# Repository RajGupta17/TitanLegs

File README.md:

## Description

TitanLegs is a 4 legged Quadruped robot which requires BLDC motors to actuate. And this is a 4 layered BLDC Servo Controller PCB which can operate upto 60V; 100A. This board has in-built micro-controller (ESP32), Gate Driver (DRV8323RS) that drives the BLDC Motor, High Voltage MOSFETs, Encoders (AS5047P), CAN BUS IC, 60V to 3.3V (2.5A) Buck Converter (TPS54260), USB to UART (CP2102) communication for programming ESP32 with Type-C, and few internal circuitry.

## 3D Model:

## Schematic Design:

## PCB Layers:

### All Layers

## Mentor

* [Chinmay Lonkar](https://github.com/ChinmayLonkar)

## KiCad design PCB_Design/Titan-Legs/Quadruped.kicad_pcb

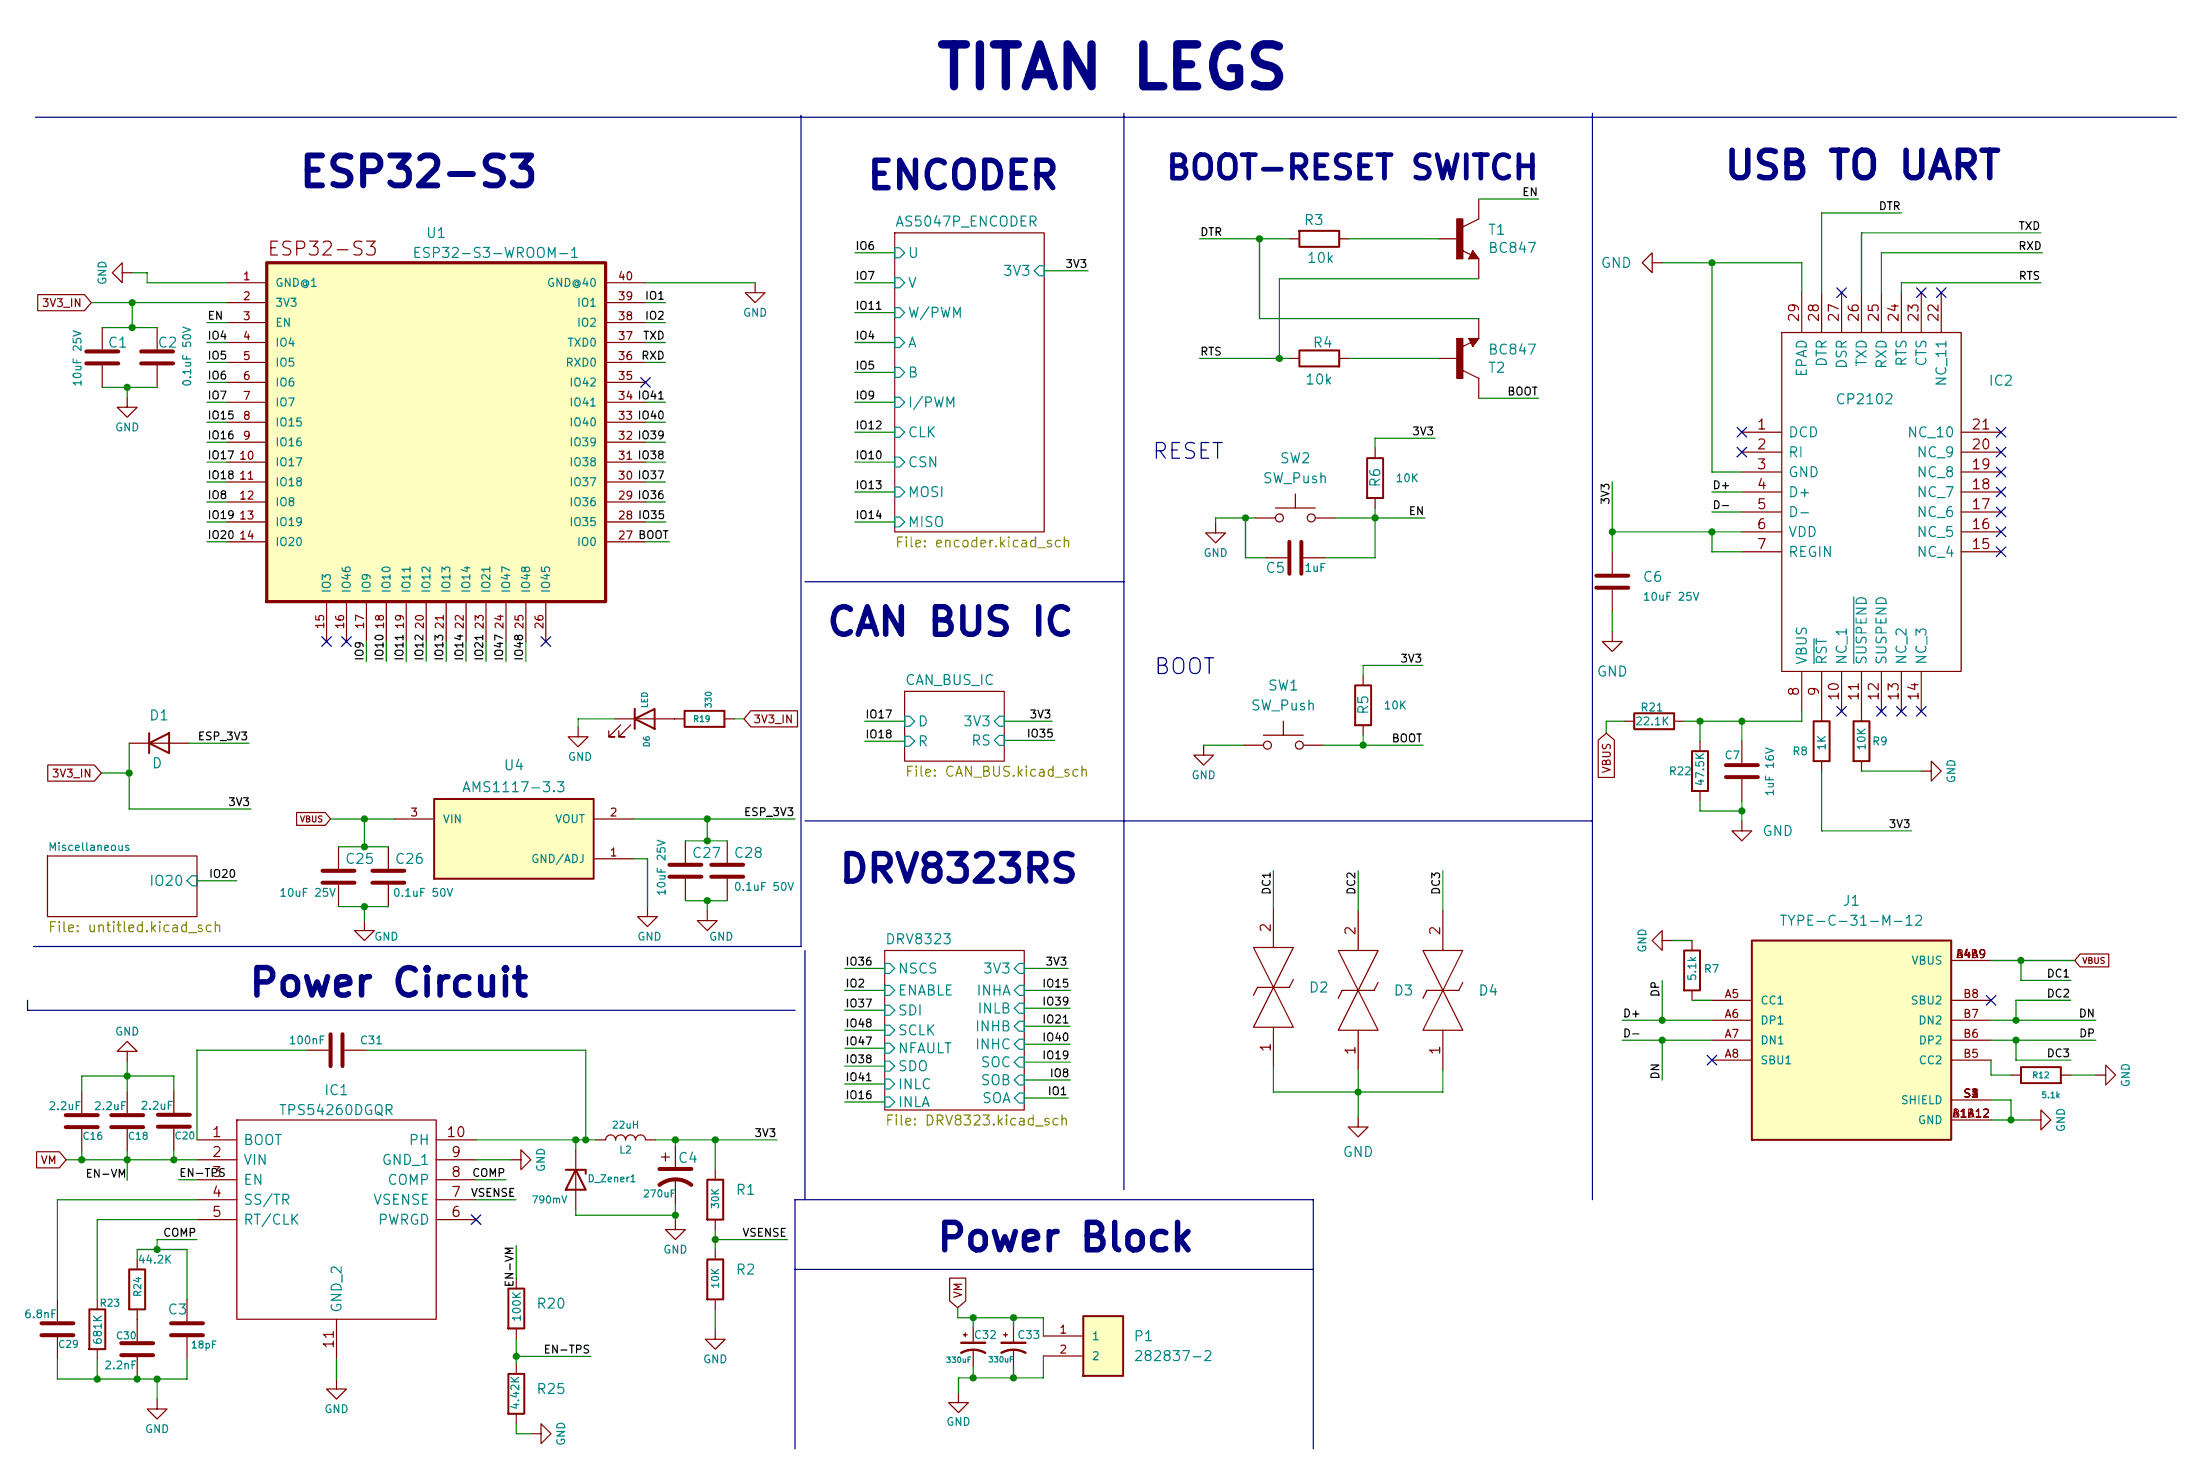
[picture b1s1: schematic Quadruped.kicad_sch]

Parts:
C1, C6, C25, C27: 10uF 25V; C_0603_1608Metric
C2, C26, C28: 0.1uF 50V; C_0603_1608Metric
C3: 18pF; C_0603_1608Metric
C4: 270uF; CP_Elec_8x10
C5: 1uF; C_0603_1608Metric
C7: 1uF 16V; C_0603_1608Metric
C16, C18, C20: 2.2uF; C_0603_1608Metric
C29: 6.8nF; C_0603_1608Metric
C30: 2.2nF; C_0603_1608Metric
C31: 100nF; C_0603_1608Metric
C32, C33: 330uF; CP_Elec_8x10
D1: D; D_SMB
D2, D3, D4: LESD5D5.0CT1G; LESD5D50CT1G; Manufacturer_Part_Number LESD5D5.0CT1G
D6: LED; LED_0402_1005Metric
D_Zener1: 790mV; D_SMB
IC1: TPS54260DGQR; IC_XTR111AIDGQR; Manufacturer_Part_Number TPS54260DGQR; Mouser Part Number 595-TPS54260DGQR
IC2: CP2102; QFN50P500X500X100-29N; Manufacturer_Part_Number CP2102; Mouser Part Number 634-CP2102
J1: TYPE-C-31-M-12; HRO_TYPE-C-31-M-12; PARTREV A
L2: 22uH; INDPM120120X800N
P1: 282837-2; TerminalBlock_bornier-2_P5.08mm
R1: 30K; R_0603_1608Metric
R2: 10K; R_0603_1608Metric
R3, R4: 10k; R_0402_1005Metric
R5, R6, R9: 10K; R_0402_1005Metric
R7, R12: 5.1k; R_0402_1005Metric
R8: 1K; R_0402_1005Metric
R19: 330; R_0402_1005Metric
R20: 100K; R_0603_1608Metric
R21: 22.1K; R_0402_1005Metric
R22: 47.5K; R_0402_1005Metric
R23: 681K; R_0603_1608Metric
R24: 44.2K; R_0603_1608Metric
R25: 4.42K; R_0603_1608Metric
SW1, SW2: SW_Push; SW_TL1015AF160QG
T1, T2: BC847; SOT23
U1: ESP32-S3-WROOM-1; MPN ESP32-S3-WROOM-1-N8R8
U4: AMS1117-3.3; SOT229P700X180-4N; PARTREV N/A

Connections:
3V3_IN: C1.1, C2.1, C4.1, C6.1, D1.1 (K), IC2.6 (VDD), IC2.7 (REGIN), L2.2, R1.1, R5.1, R6.1, R8.2, R19.2, U1.2 (3V3); also elsewhere on the board
/BOOT: R5.2, SW1.2, T2.3, U1.27 (IO0)
/COMP: C3.1, IC1.8 (COMP), R24.1
/D+: D4.2, IC2.4 (D+), J1.A6 (DP1), J1.B6 (DP2)
/D-: D3.2, IC2.5 (D-), J1.A7 (DN1), J1.B7 (DN2)
/DTR: IC2.28 (DTR), R3.2, T2.2
/EN: C5.2, R6.2, SW2.2, T1.3, U1.3 (EN)
/EN-TPS: IC1.3 (EN), R20.2, R25.1
/ESP_3V3: C27.1, C28.1, D1.2 (A), U4.2 (VOUT)
/IO1: U1.39 (IO1); also elsewhere on the board
/IO2: U1.38 (IO2); also elsewhere on the board
/IO4: U1.4 (IO4); also elsewhere on the board
/IO5: U1.5 (IO5); also elsewhere on the board
/IO6: U1.6 (IO6); also elsewhere on the board
/IO7: U1.7 (IO7); also elsewhere on the board
/IO8: U1.12 (IO8); also elsewhere on the board
/IO9: U1.17 (IO9); also elsewhere on the board
/IO10: U1.18 (IO10); also elsewhere on the board
/IO11: U1.19 (IO11); also elsewhere on the board
/IO12: U1.20 (IO12); also elsewhere on the board
/IO13: U1.21 (IO13); also elsewhere on the board
/IO14: U1.22 (IO14); also elsewhere on the board
/IO15: U1.8 (IO15); also elsewhere on the board
/IO16: U1.9 (IO16); also elsewhere on the board
/IO17: U1.10 (IO17); also elsewhere on the board
/IO18: U1.11 (IO18); also elsewhere on the board
/IO19: U1.13 (IO19); also elsewhere on the board
/IO20: U1.14 (IO20); also elsewhere on the board
/IO21: U1.23 (IO21); also elsewhere on the board
/IO35: U1.28 (IO35); also elsewhere on the board
/IO36: U1.29 (IO36); also elsewhere on the board
/IO37: U1.30 (IO37); also elsewhere on the board
/IO38: U1.31 (IO38); also elsewhere on the board
/IO39: U1.32 (IO39); also elsewhere on the board
/IO40: U1.33 (IO40); also elsewhere on the board
/IO41: U1.34 (IO41); also elsewhere on the board
/IO47: U1.24 (IO47); also elsewhere on the board
/IO48: U1.25 (IO48); also elsewhere on the board
/RTS: IC2.24 (RTS), R4.1, T1.2
/RXD: IC2.25 (RXD), U1.36 (RXD0)
/TXD: IC2.26 (TXD), U1.37 (TXD0)
/VSENSE: IC1.7 (VSENSE), R1.2, R2.1
GND: C1.2, C2.2, C3.2, C4.2, C5.1, C6.2, C7.2, C16.1, C18.1, C20.1, C25.2, C26.2, C27.2, C28.2, C29.2, C30.2, C32.2, C33.2, D2.1, D3.1, D4.1, D6.1 (K), D_Zener1.2 (A), IC1.9 (GND_1), IC1.11 (GND_2), IC1.13, IC1.14, IC2.3 (GND), IC2.29 (EPAD), J1.A1B12 (GND), J1.B1A12 (GND), J1.S1 (SHIELD), J1.S2 (SHIELD), J1.S3 (SHIELD), J1.S4 (SHIELD), P1.2, R2.2, R7.1, R9.2, R12.2, R22.2, R23.2, R25.2, SW1.1, SW2.1, U1.1 (GND@1), U1.40 (GND@40), U4.1 (GND/ADJ); also elsewhere on the board
unnamed: C7.1, IC2.8 (VBUS), R21.2, R22.1
unnamed: C29.1, IC1.4 (SS/TR)
unnamed: C30.1, R24.2
unnamed: C31.1, IC1.1 (BOOT)
unnamed: C31.2, D_Zener1.1 (K), IC1.10 (PH), L2.1
unnamed: D6.2 (A), R19.1
unnamed: IC1.5 (RT/CLK), R23.1
unnamed: IC2.9 (~RST), R8.1
unnamed: IC2.11 (~SUSPEND), R9.1
unnamed: J1.A5 (CC1), R7.2
unnamed: J1.B5 (CC2), R12.1
unnamed: R3.1, T1.1
unnamed: R4.2, T2.1
VBUS: C25.1, C26.1, D2.2, J1.A4B9 (VBUS), J1.B4A9 (VBUS), R21.1, U4.3 (VIN)
VM: C16.2, C18.2, C20.2, C32.1, C33.1, IC1.2 (VIN), P1.1, R20.1; also elsewhere on the board

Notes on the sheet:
ENCODER
CAN BUS IC
TITAN LEGS
BOOT
BOOT-RESET SWITCH
DRV8323RS
ESP32-S3
RESET
USB TO UART
Power Circuit
Power Block

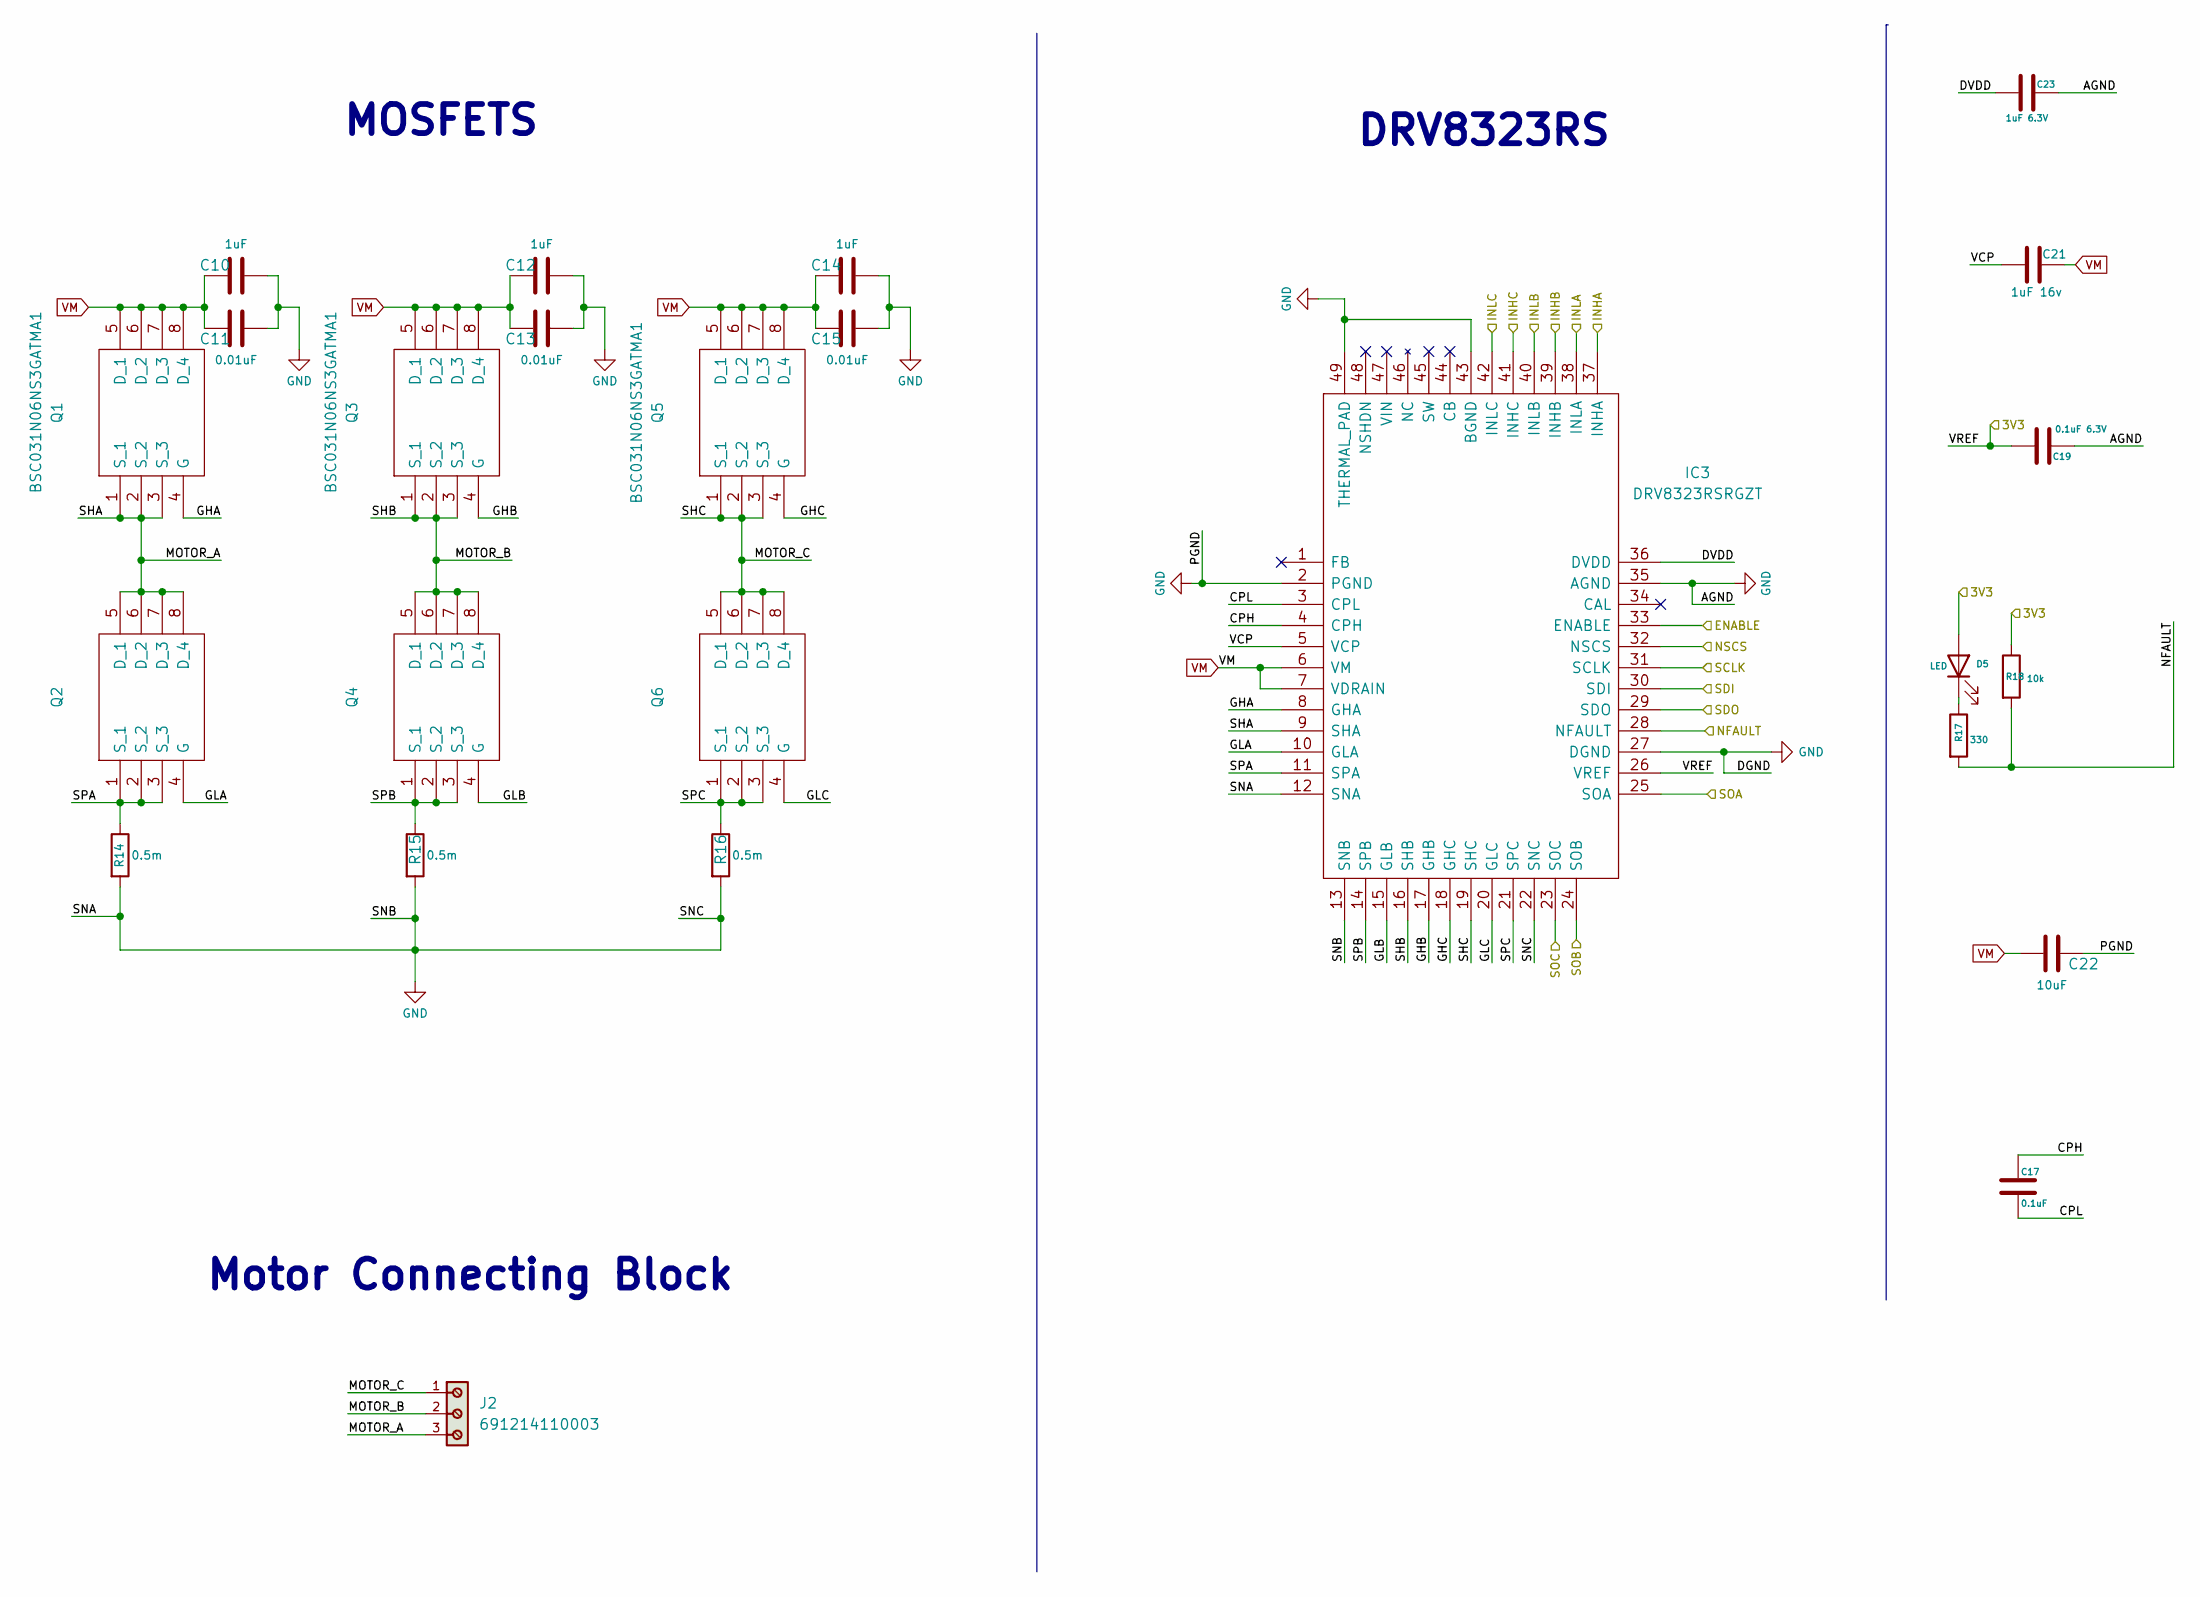
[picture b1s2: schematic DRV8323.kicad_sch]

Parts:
C10, C12, C14: 1uF; C_0603_1608Metric
C11, C13, C15: 0.01uF; C_0603_1608Metric
C17: 0.1uF; C_0603_1608Metric
C19: 0.1uF 6.3V; C_0603_1608Metric
C21: 1uF 16v; C_0603_1608Metric
C22: 10uF; C_0603_1608Metric
C23: 1uF 6.3V; C_0603_1608Metric
D5: LED; LED_0402_1005Metric
IC3: DRV8323RSRGZT; QFN50P700X700X100-49N-D; Manufacturer_Part_Number DRV8323RSRGZT; Mouser Part Number 595-DRV8323RSRGZT
J2: 691214110003; TerminalBlock_bornier-3_P5.08mm; PART-NUMBER 691214110003
Q1, Q2, Q3, Q4, Q5, Q6: BSC031N06NS3GATMA1; PG-TDSON-8_1; Manufacturer_Part_Number BSC031N06NS3GATMA1
R14, R15, R16: 0.5m; R_0.5m
R17: 330; R_0402_1005Metric
R18: 10k; R_0402_1005Metric

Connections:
3V3_IN: C19.1, D5.2 (A), IC3.26 (VREF), R18.1; also elsewhere on the board
/DRV8323/CPH: C17.2, IC3.4 (CPH)
/DRV8323/CPL: C17.1, IC3.3 (CPL)
/DRV8323/DVDD: C23.1, IC3.36 (DVDD)
/DRV8323/GHA: IC3.8 (GHA), Q1.4 (G)
/DRV8323/GHB: IC3.17 (GHB), Q3.4 (G)
/DRV8323/GHC: IC3.18 (GHC), Q5.4 (G)
/DRV8323/GLA: IC3.10 (GLA), Q2.4 (G)
/DRV8323/GLB: IC3.15 (GLB), Q4.4 (G)
/DRV8323/GLC: IC3.20 (GLC), Q6.4 (G)
/DRV8323/MOTOR_A: IC3.9 (SHA), J2.3, Q1.1 (S_1), Q1.2 (S_2), Q1.3 (S_3), Q2.5 (D_1), Q2.6 (D_2), Q2.7 (D_3), Q2.8 (D_4)
/DRV8323/MOTOR_B: IC3.16 (SHB), J2.2, Q3.1 (S_1), Q3.2 (S_2), Q3.3 (S_3), Q4.5 (D_1), Q4.6 (D_2), Q4.7 (D_3), Q4.8 (D_4)
/DRV8323/MOTOR_C: IC3.19 (SHC), J2.1, Q5.1 (S_1), Q5.2 (S_2), Q5.3 (S_3), Q6.5 (D_1), Q6.6 (D_2), Q6.7 (D_3), Q6.8 (D_4)
/DRV8323/SPA: IC3.11 (SPA), Q2.1 (S_1), Q2.2 (S_2), Q2.3 (S_3), R14.1
/DRV8323/SPB: IC3.14 (SPB), Q4.1 (S_1), Q4.2 (S_2), Q4.3 (S_3), R15.1
/DRV8323/SPC: IC3.21 (SPC), Q6.1 (S_1), Q6.2 (S_2), Q6.3 (S_3), R16.1
/DRV8323/VCP: C21.1, IC3.5 (VCP)
/IO1: IC3.25 (SOA); also elsewhere on the board
/IO2: IC3.33 (ENABLE); also elsewhere on the board
/IO8: IC3.24 (SOB); also elsewhere on the board
/IO15: IC3.37 (INHA); also elsewhere on the board
/IO16: IC3.38 (INLA); also elsewhere on the board
/IO19: IC3.23 (SOC); also elsewhere on the board
/IO21: IC3.39 (INHB); also elsewhere on the board
/IO36: IC3.32 (NSCS); also elsewhere on the board
/IO37: IC3.30 (SDI); also elsewhere on the board
/IO38: IC3.29 (SDO); also elsewhere on the board
/IO39: IC3.40 (INLB); also elsewhere on the board
/IO40: IC3.41 (INHC); also elsewhere on the board
/IO41: IC3.42 (INLC); also elsewhere on the board
/IO47: IC3.28 (NFAULT), R17.2, R18.2; also elsewhere on the board
/IO48: IC3.31 (SCLK); also elsewhere on the board
GND: C10.2, C11.2, C12.2, C13.2, C14.2, C15.2, C19.2, C22.2, C23.2, IC3.2 (PGND), IC3.12 (SNA), IC3.13 (SNB), IC3.22 (SNC), IC3.27 (DGND), IC3.35 (AGND), IC3.43 (BGND), IC3.49 (THERMAL_PAD), R14.2, R15.2, R16.2; also elsewhere on the board
unnamed: D5.1 (K), R17.1
VM: C10.1, C11.1, C12.1, C13.1, C14.1, C15.1, C21.2, C22.1, IC3.6 (VM), IC3.7 (VDRAIN), Q1.5 (D_1), Q1.6 (D_2), Q1.7 (D_3), Q1.8 (D_4), Q3.5 (D_1), Q3.6 (D_2), Q3.7 (D_3), Q3.8 (D_4), Q5.5 (D_1), Q5.6 (D_2), Q5.7 (D_3), Q5.8 (D_4); also elsewhere on the board

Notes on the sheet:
DRV8323RS
MOSFETS
Motor Connecting Block

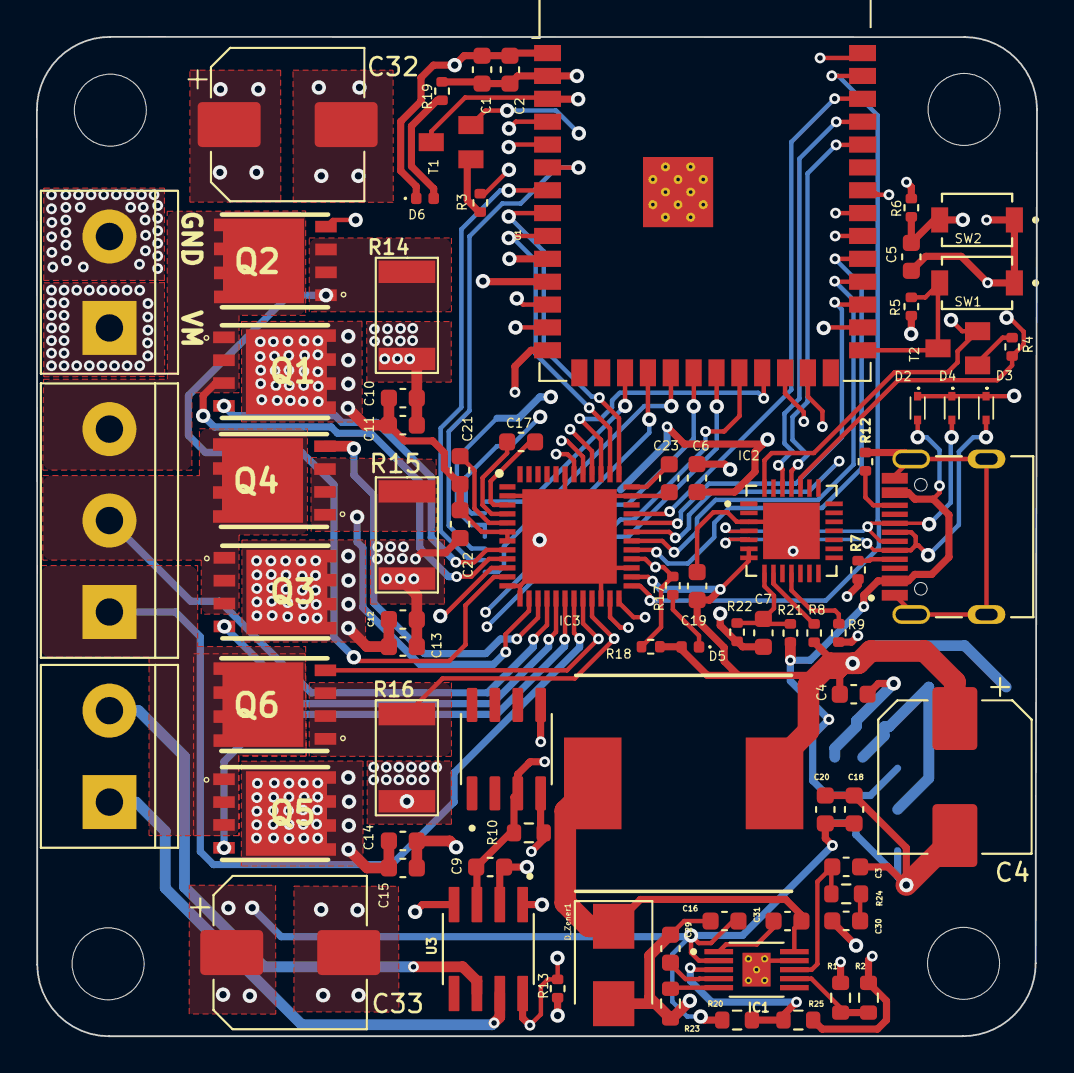
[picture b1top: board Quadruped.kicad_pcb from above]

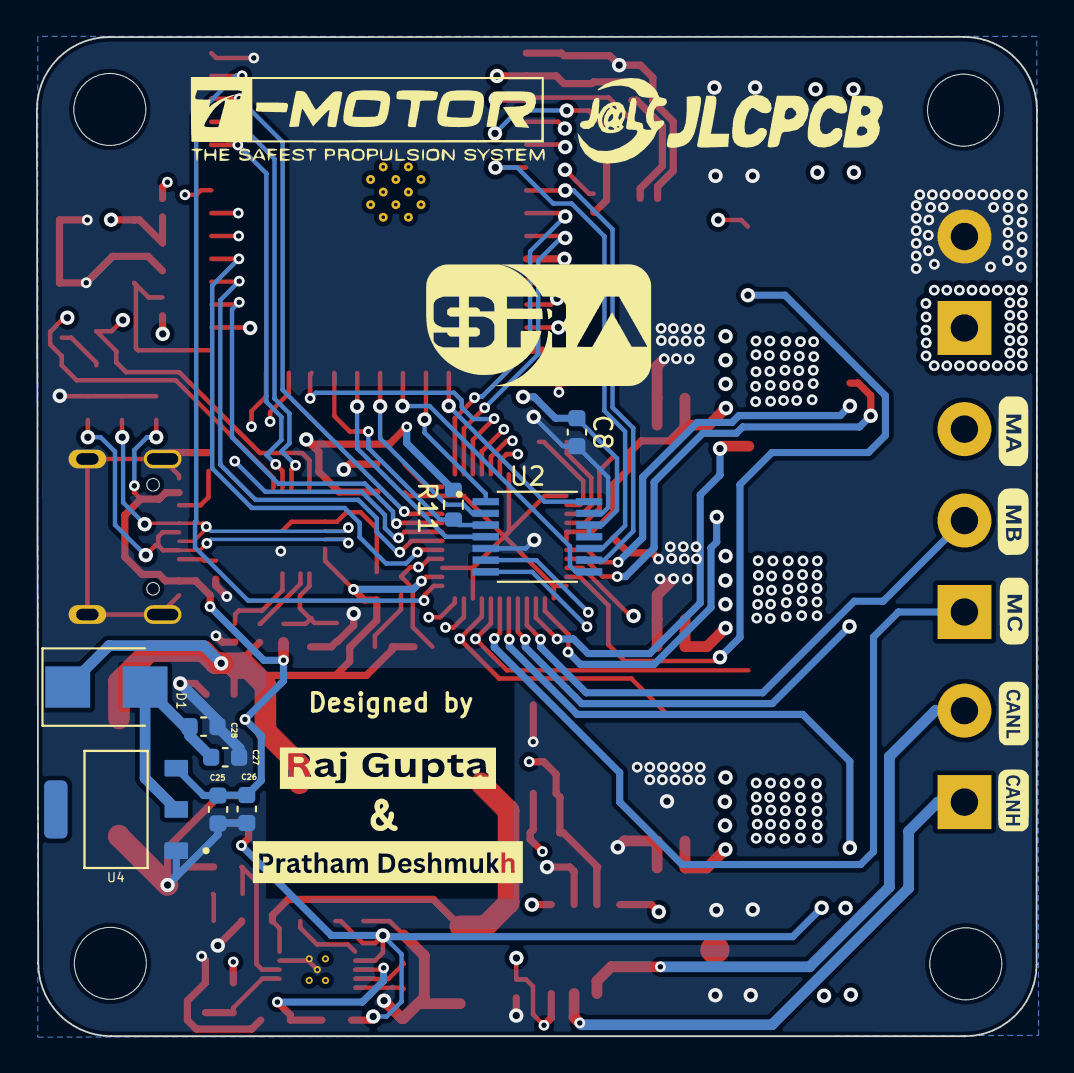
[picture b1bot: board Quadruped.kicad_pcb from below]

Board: 4 copper layers, 55.6 x 55.5 mm, 92 parts (9 on the bottom side), 77 nets.

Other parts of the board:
C4#2: 560uF; C_0603_1608Metric
C8, C9: 0.1uF; C_0603_1608Metric
H1, H2, H3, H4: MountingHole; MountingHole_4mm
P2: 282837-2; TerminalBlock_bornier-2_P5.08mm
R10: 4.7K; R_0603_1608Metric
R11: 10K; R_0603_1608Metric
R13: 10K; R_0402_1005Metric
U2: AS5047P-ATSM; SOP65P640X120-14N
U3: SN65HVD230DR; SOIC127P599X175-8N
U5: DS18S20Z+; DS18S20Z_

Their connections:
3V3_IN: C4#2.1, C8.1, C9.1, R10.1, R11.1, U2.11 (VDD), U2.12 (VDD3V3), U3.3 (VCC), U5.3 (VDD); also elsewhere on the board
/CAN_BUS_IC/CANH: P2.1, U3.7 (CANH)
/CAN_BUS_IC/CANL: P2.2, U3.6 (CANL)
/IO4: U2.7 (A); also elsewhere on the board
/IO5: U2.6 (B); also elsewhere on the board
/IO6: U2.10 (U); also elsewhere on the board
/IO7: U2.9 (V); also elsewhere on the board
/IO9: U2.14 (I/PWM); also elsewhere on the board
/IO10: U2.1 (CSN); also elsewhere on the board
/IO11: U2.8 (W/PWM); also elsewhere on the board
/IO12: U2.2 (CLK); also elsewhere on the board
/IO13: U2.4 (MOSI); also elsewhere on the board
/IO14: R11.2, U2.3 (MISO); also elsewhere on the board
/IO17: U3.1 (D); also elsewhere on the board
/IO18: U3.4 (R); also elsewhere on the board
/IO20: R10.2, U5.4 (DQ); also elsewhere on the board
/IO35: R13.1, U3.8 (RS); also elsewhere on the board
GND: C4#2.2, C8.2, C9.2, R13.2, U2.5 (TEST), U2.13 (GND), U3.2 (GND), U5.5 (GND); also elsewhere on the board

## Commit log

2023-02-07 schematics completed
2023-02-07 schematics 1st iteration completed
2023-02-07 Schematics 2nd Iteration Completed
2023-02-07 Added AMS1117 for ESP32-S3
2023-02-08 updated minor changes
2023-02-09 added electrolytic capacitors
2023-02-10 footprint assignment done
2023-02-12 DRV8323 and CP2102 routing initiated
2023-02-20 updating recent changes
2023-02-28 Copper filled VM to mosfets
2023-03-01 gpio pins updated
2023-03-02 Remove unnecessary files in component libraries
2023-03-03 Add new placement for Quadruped PCB
2023-03-04 Added high voltage copper fills
2023-03-04 Added Complete ESP32 net traces
2023-03-05 Added DRV8323RS Traces and some minor changes
2023-03-05 Completed PCB Routing
2023-03-05 Added Changes after First Review
2023-03-19 Merged silkscreen changes and completed final prototype
2023-03-20 removed unnecessary files
2023-03-20 Merged the silkscreen MA,MB,MC and added vias in shunt resistors
2023-03-20 Merged the silkscreen MA,MB,MC and added more vias in shunt resistors
2023-03-20 Added JLCPCB Logo on Back Silkscreen and final Changes Merged
2023-04-04 Added Electrolytic Capacitor for TPS54260 and resisotrs for EN pin
2023-04-05 Added Electrolytic Capacitor and moved AMS1117 to B.Cu
2023-04-11 Added updated readme along with assets
2023-04-11 Added mentor section in README
2023-04-11 Added minor changes in ReadME
